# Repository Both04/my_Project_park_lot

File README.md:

# my_Project_park_lot

คณะวิทยาศาสตร์และวิศวกรรมศาตร์ ภาควิชาวิศวกรรมไฟฟ้าและคอมพิวเตอร์ 
หลักสูตร วิศวกรรมคอมพิวเตอร์ ชั้นปีที่ 2 
มหาวิทยาลัยเกษตรศาสตร์ วิทยาเขตเฉลิมพระเกียติ จังหวัดสกลนคร

ผู้จัดทำ
นายกันตณ หอทอง 6140207215
นายรัตนศักดิ์ แสนรังค์ 6140204832

โครงการที่จอดรถทันสมัย
หลักการทำงาน
จะมีอยู่2ส่วน
ส่วนที่ 1 
	มีการนับจำนวนรถด้วย LDR แบบดิจิตอล ในส่วนของ LDR จะมี LDR IN และ LDR OUT บริเวณทางเข้า เมื่อรถไปบังตัว LDR แล้วตัว Servo ก็จะทำงาน โดยตัว Servo จะเป็นตัวควบคุมการเปิด-ปิดของไม้กั้น และตัว LCD จะเป็นตัวบอกจำนวนรถที่เข้าและออก เมื่อรถเต็ม Servo จะไม่ทำงานจนกว่าจะมีที่ว่าง และ LDR อีก 2 ตัว จะเป็นการติดตั้งบริเวณที่จอดรถ เมื่อรถไปบังตัว LDR จะขึ้นสถานะว่าช่องจอดรถไม่ว่าง

ส่วนที่ 2 
	คือการจับระยะรถที่เข้าใกล้ตัว Ultrasonic เมื่อรถยิ่งเข้าใกล้ เสียงจะดังขึ้นเรื่อย ๆ ตามระดับของระยะที่จะเข้าใกล้ตัว Sensor และมี LED ช่วยแสดงสถานะของระยะที่เข้าใกล้ระหว่าง รถกับSensor
    
//////////////////////////////////////////////////////////////////////////////////////////////////////////////////////////////////////////
Faculty of Science and Engineering, Department of Electrical and Computer Engineering
2nd year computer engineering course
Kasetsart University, Chalermprakiet Campus, Sakon Nakhon Province

Provider
Mr Kantan Horthong 6140207215
Mr. Rattanasak Saenrang 6140204832

Modern car park project
Principles
There will be 2 parts
Part 1
There are a lot of LDRs in LDRs and LDRs have both LDR in and out of the LDR area and the Servo will work on its own. The LCD will tell you the number of vehicles entering and exiting when the servo is busy and the other 2 LDRs will be installed in the parking space. LDR will depend on the busy parking space.

Part 2
Ultrasonic sensor, when the sound signal is detected and the ultrasonic sensor when there is noise, the sensor will have an LED to show the distance between the sensors

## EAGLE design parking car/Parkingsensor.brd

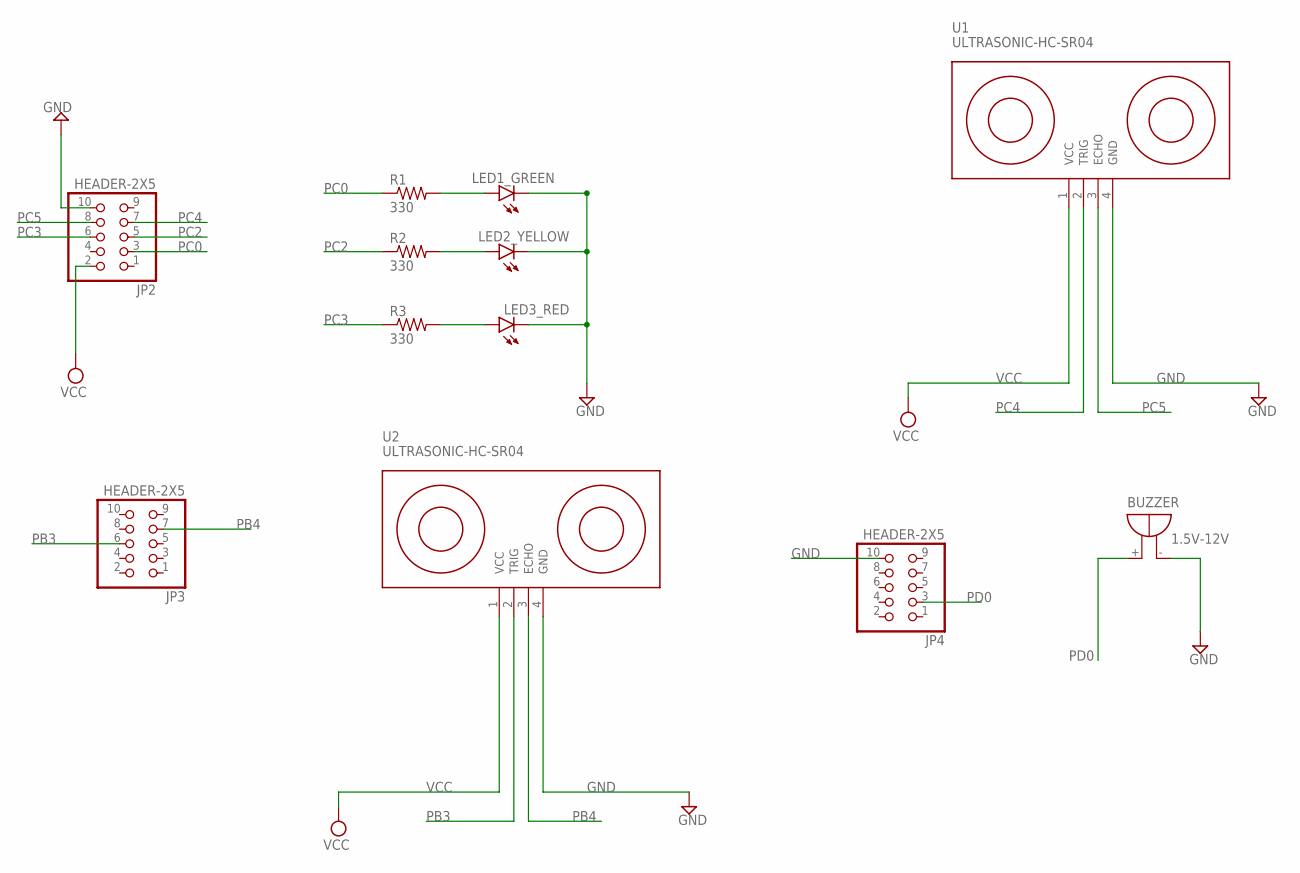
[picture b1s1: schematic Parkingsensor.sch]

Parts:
BUZZER: 1.5V-12V; EB2209A
JP2, JP3, JP4: HEADER-2X5; 2X05
LED1_GREEN, LED2_YELLOW, LED3_RED: LED3MM
R1, R2, R3: 330; 0207/10
U1, U2: ULTRASONIC-HC-SR04

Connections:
GND: BUZZER.-, JP2.10, JP4.10, LED1_GREEN.K (C), LED2_YELLOW.K (C), LED3_RED.K (C), U1.4 (GND), U2.4 (GND)
unnamed: LED1_GREEN.A, R1.2
unnamed: LED2_YELLOW.A, R2.2
unnamed: LED3_RED.A, R3.2
PB3: JP3.6, U2.2 (TRIG)
PB4: JP3.7, U2.3 (ECHO)
PC0: JP2.3, R1.1
PC2: JP2.5, R2.1
PC3: JP2.6, R3.1
PC4: JP2.7, U1.2 (TRIG)
PC5: JP2.8, U1.3 (ECHO)
PD0: BUZZER.+, JP4.3
VCC: JP2.2, U1.1 (VCC), U2.1 (VCC)

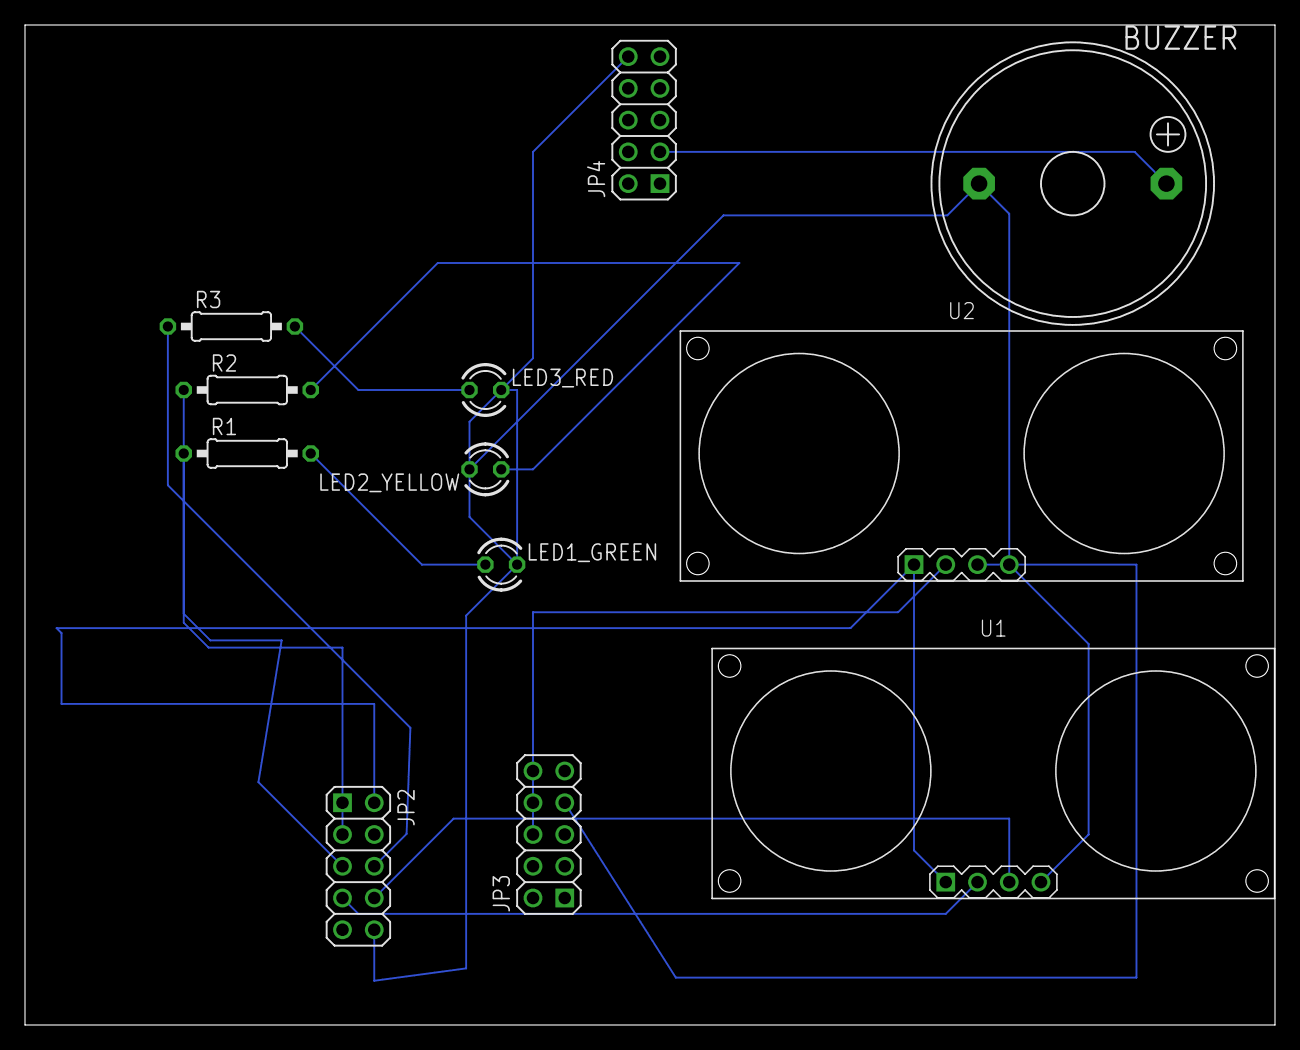
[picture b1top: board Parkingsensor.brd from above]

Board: 2 copper layers, 100.0 x 80.0 mm, 12 parts (0 on the bottom side), 13 nets.

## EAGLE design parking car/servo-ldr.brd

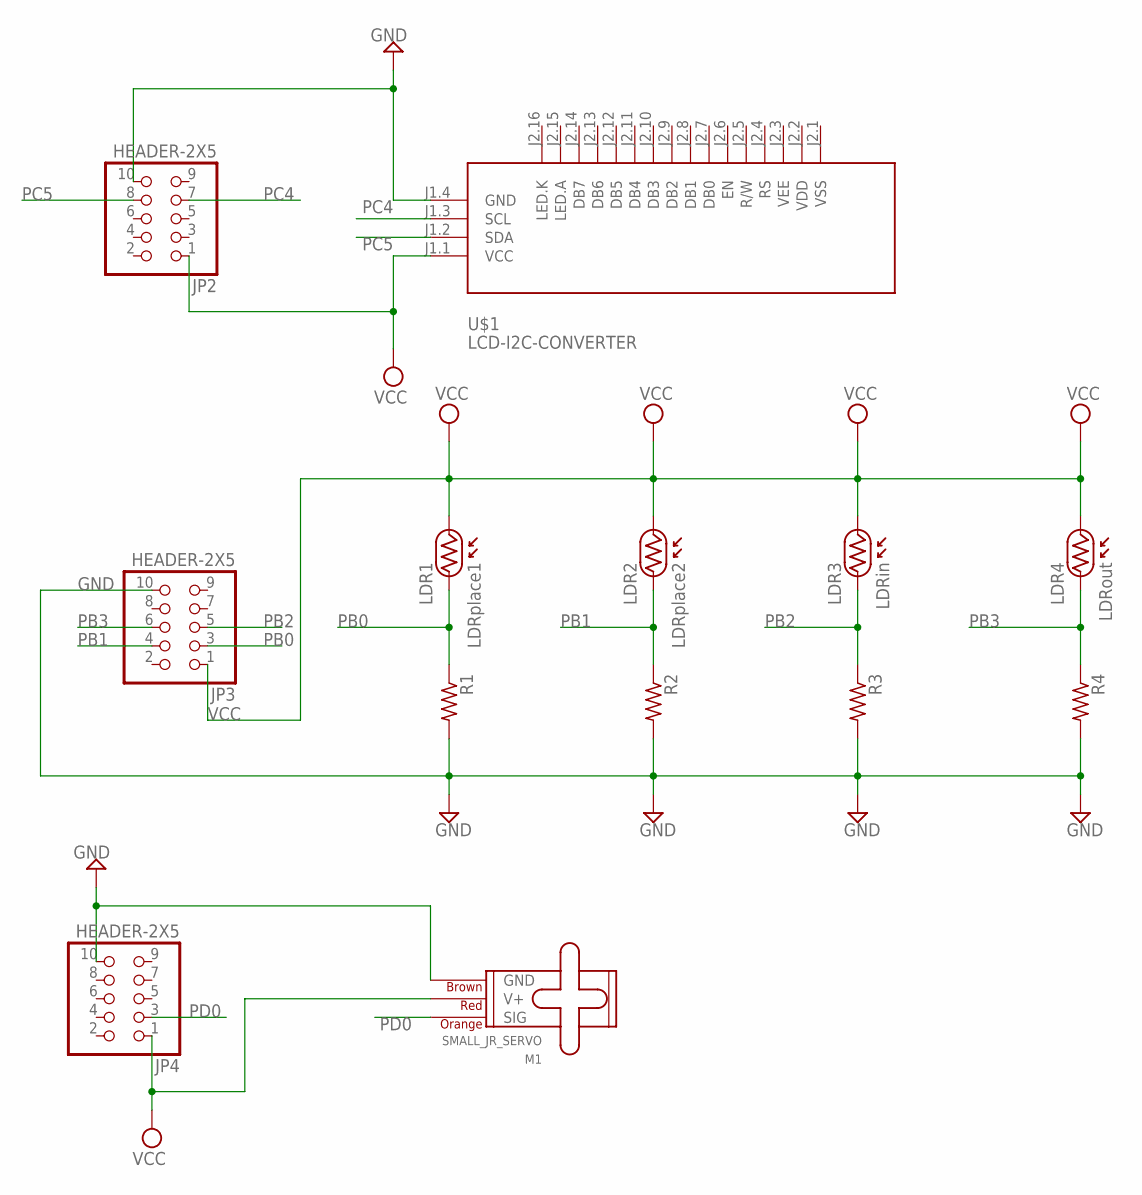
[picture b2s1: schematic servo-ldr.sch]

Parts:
JP2, JP3, JP4: HEADER-2X5; 2X05
LDR1: LDRplace1; 3MM
LDR2: LDRplace2; 3MM
LDR3: LDRin; 3MM
LDR4: LDRout; 3MM
M1: SMALL_JR_SERVO; 1X03
R1, R2, R3, R4: R-US_0207/10; 0207/10
U$1: LCD-I2C-CONVERTER

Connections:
GND: JP2.10, JP3.10, JP4.10, M1.3 (GND), R1.2, R2.2, R3.2, R4.2, U$1.J1.4 (GND)
PB0: JP3.3, LDR1.P$2, R1.1
PB1: JP3.4, LDR2.P$2, R2.1
PB2: JP3.5, LDR3.P$2, R3.1
PB3: JP3.6, LDR4.P$2, R4.1
PC4: JP2.7, U$1.J1.3 (SCL)
PC5: JP2.8, U$1.J1.2 (SDA)
PD0: JP4.3, M1.1 (SIG)
VCC: JP2.1, JP3.1, JP4.1, LDR1.P$1, LDR2.P$1, LDR3.P$1, LDR4.P$1, M1.2 (V+), U$1.J1.1 (VCC)

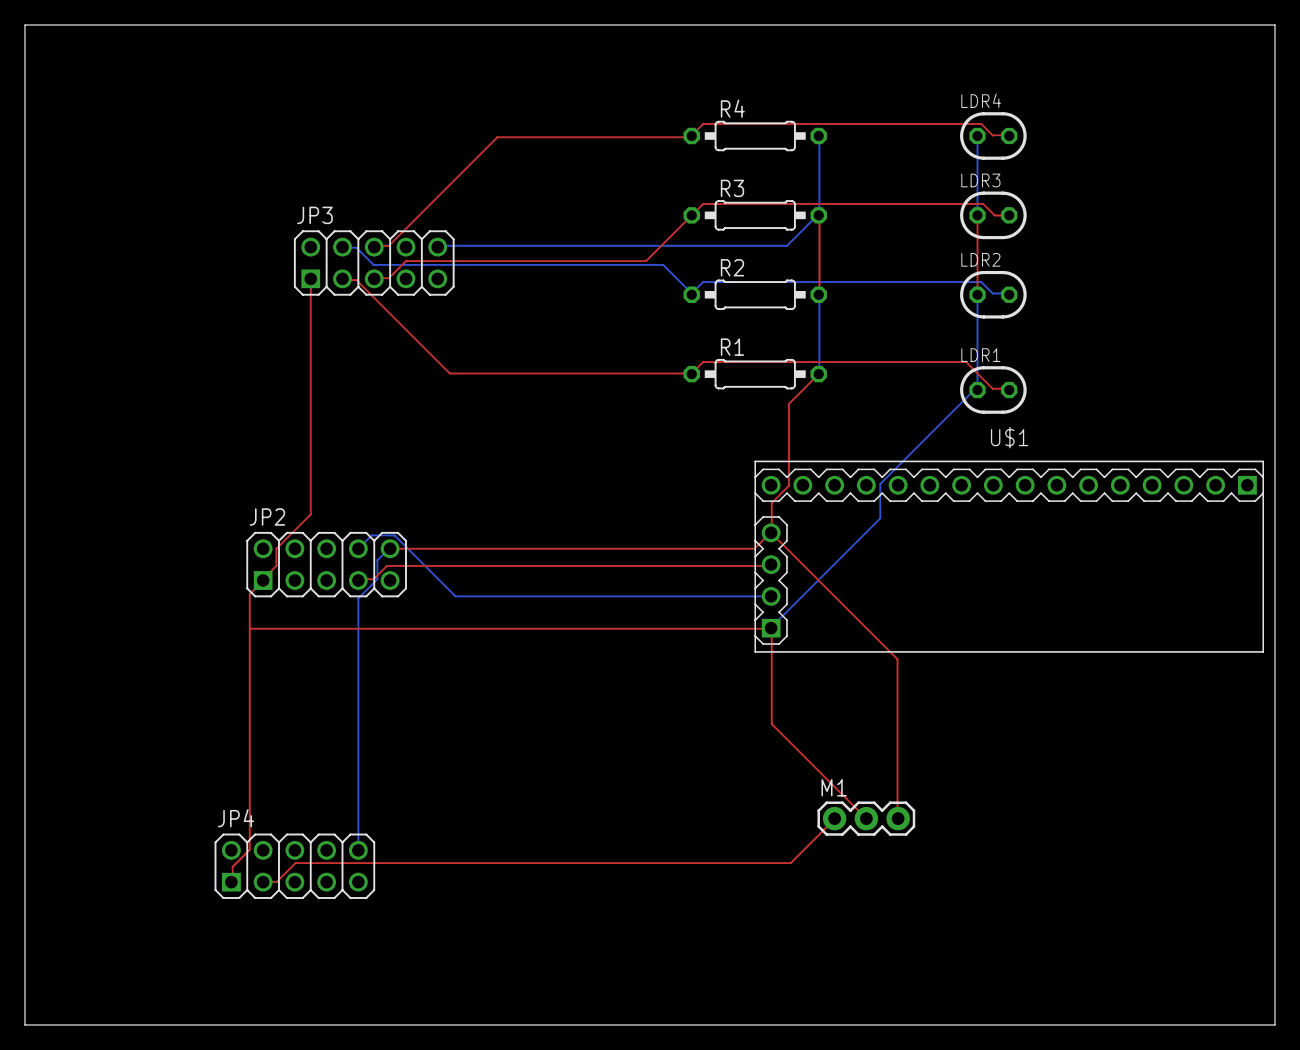
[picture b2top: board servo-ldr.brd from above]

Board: 2 copper layers, 100.0 x 80.0 mm, 13 parts (0 on the bottom side), 9 nets.

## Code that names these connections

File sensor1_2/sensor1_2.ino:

#define trig1 PIN_PC4
#define echo1 PIN_PC5

#define trig2 PIN_PB3
#define echo2 PIN_PB4


#define green PIN_PC0
#define yellow PIN_PC2
#define red PIN_PC3


#define buzz PIN_PD0

int duration1;
int duration2;
float distance1;
float distance2;

void setup() {
  pinMode(trig1, OUTPUT);
  digitalWrite(trig1, LOW);
  delayMicroseconds(2);
  pinMode(echo1, INPUT);

  pinMode(trig2, OUTPUT);
  digitalWrite(trig2, LOW);
  delayMicroseconds(2);
  pinMode(echo2, INPUT);
  delay(6000);
  
  pinMode(buzz, OUTPUT);
  
  pinMode(green, OUTPUT);
  pinMode(yellow, OUTPUT);
  pinMode(red, OUTPUT);

}

void sensor1(){
  int i=20;
  digitalWrite(trig1, HIGH);
  delayMicroseconds(10);
  digitalWrite(trig1, LOW);
  duration1 = pulseIn(echo1, HIGH);
  distance1 = duration1/58;

  if (distance1 <= 15 && distance1 >= 6.5) {
    digitalWrite(green, HIGH);
    digitalWrite(yellow, LOW);
    digitalWrite(red, LOW);
  } 
  else if(distance1 <= 7 && distance1 >= 5) {
    digitalWrite(green, LOW);
    digitalWrite(yellow, HIGH);
    digitalWrite(red, LOW);
  } 
  else if(distance1 <= 4.5 && distance1 >= 3){
    digitalWrite(green, LOW);
    digitalWrite(yellow, LOW);
    digitalWrite(red, HIGH);
  }
  else if(distance1 <= 2 && distance1 >= 1.5){
    digitalWrite(green, LOW);
    digitalWrite(yellow, LOW);
    digitalWrite(red, LOW);
  }
  
  else {
    digitalWrite(green, LOW);
    digitalWrite(yellow, LOW);
    digitalWrite(red, LOW);
  }

  if(distance1<=15 && distance1 >= 2.5 ) {
    i=distance1*i;
  digitalWrite(buzz, HIGH);
    delay(i);
  digitalWrite(buzz, LOW);
    delay(i);
  }
  delay(5);
}
void sensor2(){
  int l=20;
  digitalWrite(trig2, HIGH);
  delayMicroseconds(10);
  digitalWrite(trig2, LOW);
  duration2 = pulseIn(echo2, HIGH);
  distance2 = duration2/58;

  if (distance2 <= 15 && distance2 >= 6.5) {
    digitalWrite(green, HIGH);
    digitalWrite(yellow, LOW);
    digitalWrite(red, LOW);
  } 
  else if(distance2 <= 7 && distance2 >= 5) {
    digitalWrite(green, LOW);
    digitalWrite(yellow, HIGH);
    digitalWrite(red, LOW);
  } 
  else if(distance2 <= 4.5 && distance2 >= 3){
    digitalWrite(green, LOW);
    digitalWrite(yellow, LOW);
    digitalWrite(red, HIGH);
  }
  else if(distance2 <= 2 && distance2 >= 1.5){
    digitalWrite(green, LOW);
    digitalWrite(yellow, LOW);
    digitalWrite(red, LOW);
  }
  
  else {
    digitalWrite(green, LOW);
    digitalWrite(yellow, LOW);
    digitalWrite(red, LOW);
  }

  if(distance2<=15 && distance2 >= 2.5 ) {
    l=distance2*l;
  digitalWrite(buzz, HIGH);
    delay(l);
  digitalWrite(buzz, LOW);
    delay(l);
  }
  delay(5);
}

void loop() {
  sensor1();
  sensor2();
  delay(100); 
}

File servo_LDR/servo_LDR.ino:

#include <Servo.h>
#include <Wire.h>
#include <LCD.h> 
#include <LiquidCrystal_I2C.h>
Servo myservo;
int y=0; 
#define I2C_ADDR 0x27
#define light_PIN 3

LiquidCrystal_I2C lcd(I2C_ADDR,2,1,0,4,5,6,7);

byte val[8];
const int LDRplace[]={PIN_PB0,PIN_PB1};
const int LDRout = PIN_PB2;
const int LDRin = PIN_PB3;
int count=0;
int valin=0;
int valout=0;
int pos = 0; 
void setup() {
  lcd.setBacklightPin(light_PIN,POSITIVE);
  lcd.setBacklight(HIGH);
  lcd.begin(16, 2);  
  for(int i=0;i<2;i++){
    pinMode(LDRplace[i], INPUT);
  }
  pinMode(LDRin, INPUT);
  pinMode(LDRout, INPUT);
  myservo.attach(PIN_PD0); 
  myservo.write(pos);
  
  for (pos = 0; pos <= 90; pos += 1) { 
    myservo.write(pos);              
    delay(30);                       
  }
  delay(1000);
  for (pos = 90; pos >= 0; pos -= 1) { 
    myservo.write(pos);             
    delay(30);                       
  }
  lcd.clear();
  lcd.setCursor(0, 0);
  count=0;
}

void loop() {
 //******************************************************* 
  lcd.setCursor(0, 0);
  lcd.print("P-L:");
  lcd.setCursor(0, 1);
  for( y=0;y<2;y++)
     {      
      val[y]=digitalRead(LDRplace[y]);
      if(val[y]==1){
        lcd.print(y+1);
      }            
      }
       
      lcd.print("       ");        
  valin=digitalRead(LDRin);
  valout=digitalRead(LDRout);
 
  if(count>=2){
    count=2;
    myservo.write(pos);
    delay(500);
    myservo.detach();
    lcd.setCursor(5, 1);
    lcd.print("       full");}
  
 //******************************************************** 
  if(valout==LOW){
    for (pos = 0; pos <= 90; pos += 1) { 
      myservo.write(pos);
      delay(30);
    }
      while(valout==LOW){
        valout=digitalRead(LDRout);
      }
        count++;
        if(count<3){ 
        }
    delay(1000);     
    for (pos = 90; pos >= 0; pos -= 1) { 
      myservo.write(pos);
      delay(30);
    }
       }
//********************************************************       
  if(valin ==LOW){
    myservo.attach(PIN_PD0);
    for (pos = 0; pos <= 90; pos += 1) { 
      myservo.write(pos);
      delay(30);
    }
      while(valin ==LOW){
        valin=digitalRead(LDRin);
      }
        count--;
        if(count<=0){
          count=0;
        }
  delay(1000);      
  for (pos = 90; pos >= 0; pos -= 1){ 
    myservo.write(pos);delay(30);
  }        
  }
//********************************************************        
  lcd.setCursor(10, 1);
  lcd.print(" car:");
  lcd.print(count);  
  if(count>=2){
    lcd.setCursor(5, 1);
    lcd.print("       full   ");
  }

}

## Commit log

2019-11-08 Create LICENSE

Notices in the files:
parts and their libraries:
diy-modules: Released under the Creative Commons Attribution 4.0 International License: http://creativecommons.org/licenses/by/4.0
